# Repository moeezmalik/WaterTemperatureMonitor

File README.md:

# WaterTemperatureMonitor
 Simple system that monitors the temperature of bath water and displays it on a pair of 7 segment display.

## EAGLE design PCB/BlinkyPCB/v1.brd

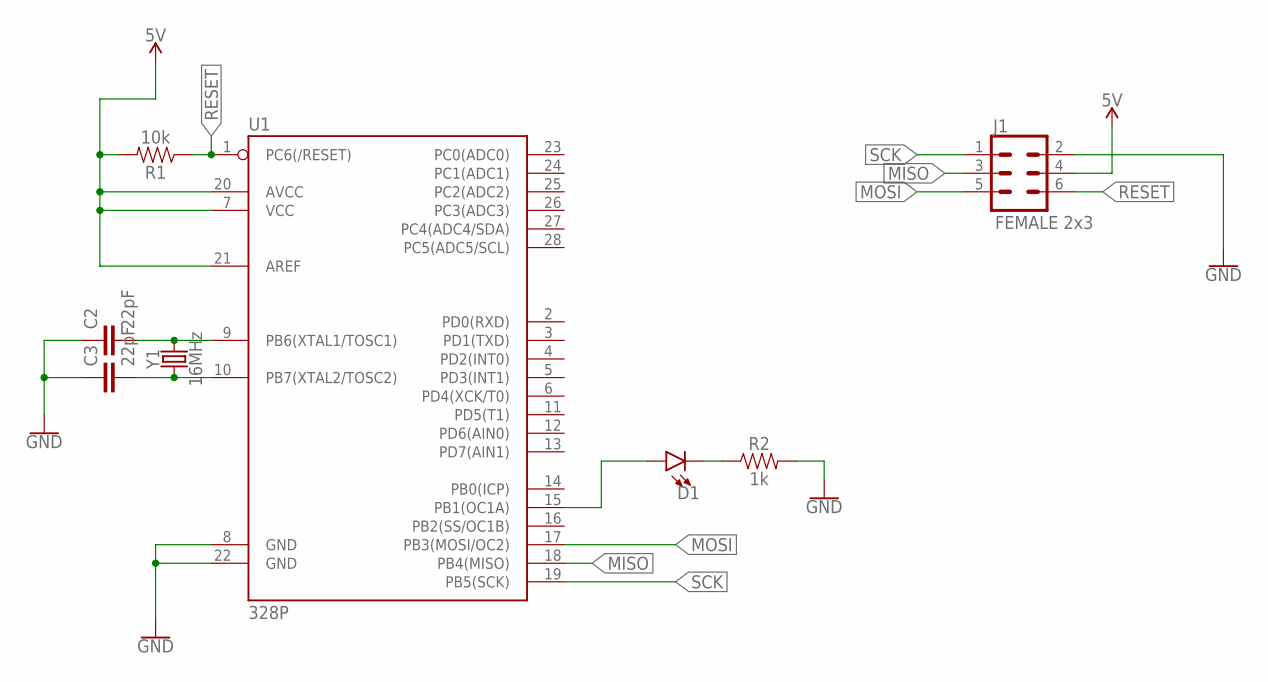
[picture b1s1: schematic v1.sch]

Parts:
C2, C3: 22pF; CAP-PTH-2.54
D1: LED3MM; LED_3MM
J1: FEMALE 2x3; 2X3
R1: 10k; AXIAL-0.3
R2: 1k; AXIAL-0.3
U1: 328P; DIP28
Y1: 16MHz; HC49US

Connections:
5V: J1.4, R1.P$2 (2), U1.7 (VCC), U1.20 (AVCC), U1.21 (AREF)
GND: C2.1, C3.1, J1.2, R2.P$2 (2), U1.8 (GND), U1.22 (GND)
MISO: J1.3, U1.18 (PB4(MISO))
MOSI: J1.5, U1.17 (PB3(MOSI/OC2))
unnamed: D1.A, U1.15 (PB1(OC1A))
unnamed: D1.K (C), R2.P$1 (1)
unnamed: C2.2, U1.9 (PB6(XTAL1/TOSC1)), Y1.2
unnamed: C3.2, U1.10 (PB7(XTAL2/TOSC2)), Y1.1
RESET: J1.6, R1.P$1 (1), U1.1 (PC6(/RESET))
SCK: J1.1, U1.19 (PB5(SCK))

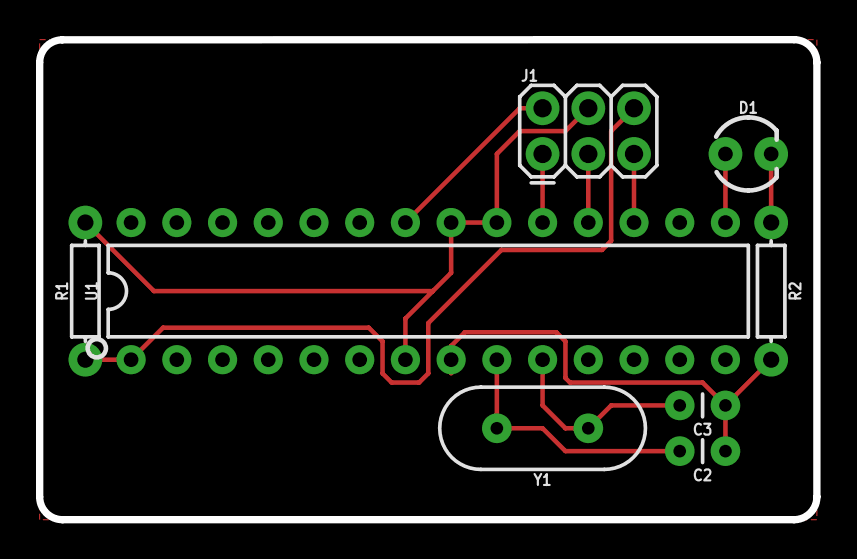
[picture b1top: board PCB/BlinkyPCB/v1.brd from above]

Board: 2 copper layers, 43.2 x 26.7 mm, 8 parts (0 on the bottom side), 10 nets.

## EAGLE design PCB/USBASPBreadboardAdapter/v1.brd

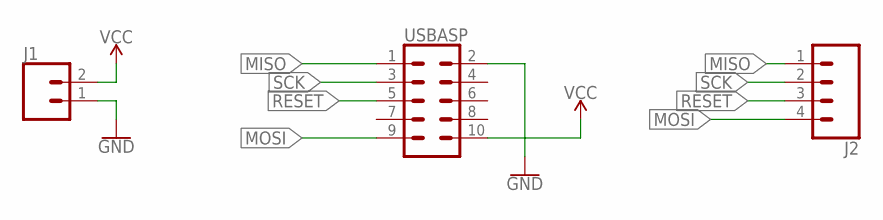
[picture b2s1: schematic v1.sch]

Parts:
J1: CONN_02; 1X02
J2: CONN_04; 1X04
USBASP: CONN_05X2PTH; 2X5

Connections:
GND: J1.1, USBASP.2
MISO: J2.1, USBASP.1
MOSI: J2.4, USBASP.9
RESET: J2.3, USBASP.5
SCK: J2.2, USBASP.3
VCC: J1.2, USBASP.10

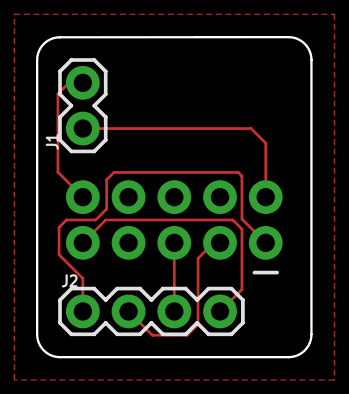
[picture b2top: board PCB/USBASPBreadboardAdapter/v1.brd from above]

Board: 2 copper layers, 15.2 x 17.8 mm, 3 parts (1 on the bottom side), 6 nets.

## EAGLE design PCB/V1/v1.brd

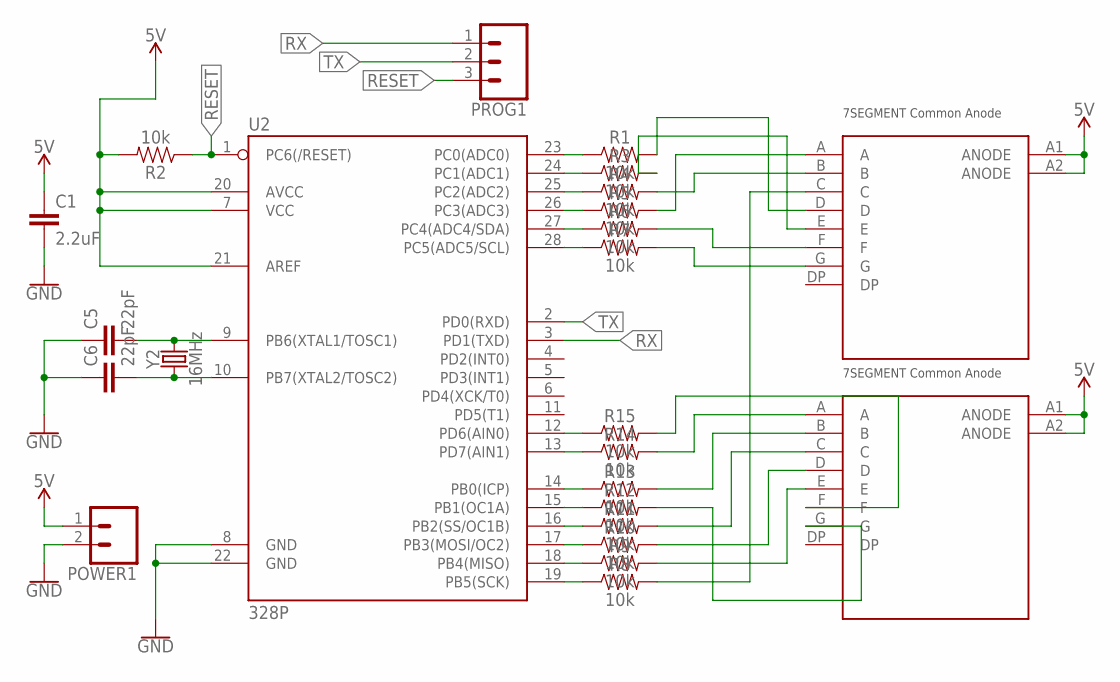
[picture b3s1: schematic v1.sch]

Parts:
C1: 2.2uF; 1206
C5, C6: 22pF; CAP-PTH-2.54
POWER1: CONN_02; 1X02
PROG1: CONN_03; 1X03
R1, R3, R4, R5, R6, R7, R8, R9, R10, R11, R12, R13, R14, R15: 10k; 0805
R2: 10k; AXIAL-0.3
U2: 328P; DIP28
U$1, U$2: 7SEGMENTCA
Y2: 16MHz; HC49US

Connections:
5V: C1.1, POWER1.1, R2.P$2 (2), U2.7 (VCC), U2.20 (AVCC), U2.21 (AREF), U$1.A1 (ANODE), U$1.A2 (ANODE), U$2.A1 (ANODE), U$2.A2 (ANODE)
GND: C1.2, C5.1, C6.1, POWER1.2, U2.8 (GND), U2.22 (GND)
unnamed: C5.2, U2.9 (PB6(XTAL1/TOSC1)), Y2.2
unnamed: C6.2, U2.10 (PB7(XTAL2/TOSC2)), Y2.1
unnamed: R1.1, U2.23 (PC0(ADC0))
unnamed: R3.1, U2.24 (PC1(ADC1))
unnamed: R4.1, U2.25 (PC2(ADC2))
unnamed: R5.1, U2.26 (PC3(ADC3))
unnamed: R6.1, U2.27 (PC4(ADC4/SDA))
unnamed: R7.1, U2.28 (PC5(ADC5/SCL))
unnamed: R7.2, U$1.G
unnamed: R6.2, U$1.F
unnamed: R5.2, U$1.A
unnamed: R4.2, U$1.B
unnamed: R3.2, U$1.E
unnamed: R1.2, U$1.D
unnamed: R8.1, U2.19 (PB5(SCK))
unnamed: R8.2, U$1.C
unnamed: R12.1, U2.15 (PB1(OC1A))
unnamed: R11.1, U2.16 (PB2(SS/OC1B))
unnamed: R10.1, U2.17 (PB3(MOSI/OC2))
unnamed: R9.1, U2.18 (PB4(MISO))
unnamed: R9.2, U$2.E
unnamed: R10.2, U$2.D
unnamed: R11.2, U$2.C
unnamed: R12.2, U$2.G
unnamed: R15.1, U2.12 (PD6(AIN0))
unnamed: R14.1, U2.13 (PD7(AIN1))
unnamed: R13.1, U2.14 (PB0(ICP))
unnamed: R15.2, U$2.F
unnamed: R14.2, U$2.A
unnamed: R13.2, U$2.B
RESET: PROG1.3, R2.P$1 (1), U2.1 (PC6(/RESET))
RX: PROG1.1, U2.3 (PD1(TXD))
TX: PROG1.2, U2.2 (PD0(RXD))

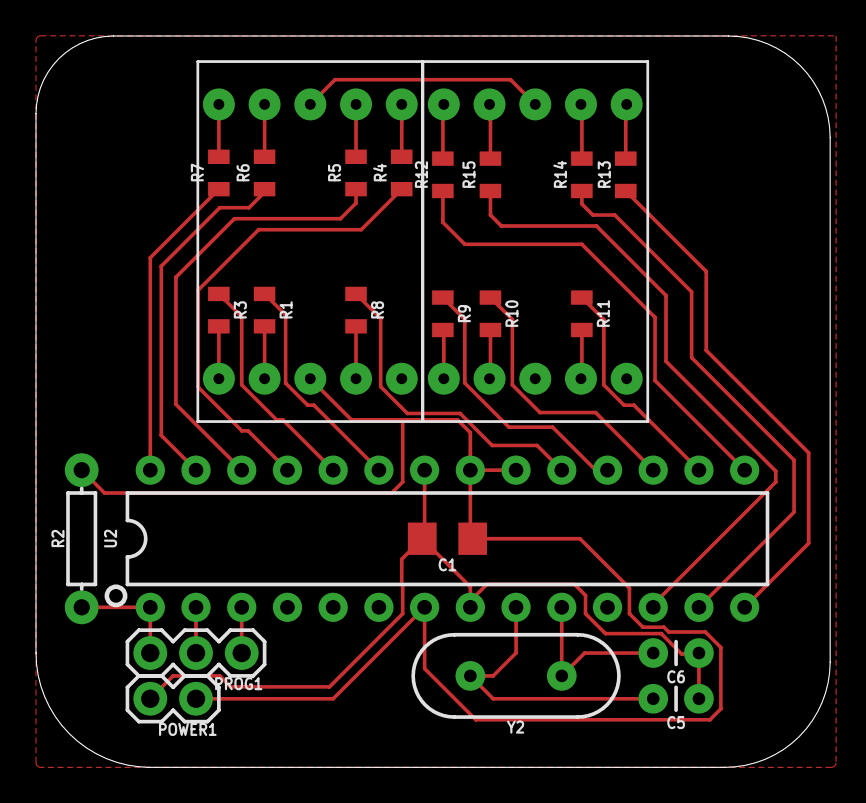
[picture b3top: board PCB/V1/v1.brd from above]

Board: 2 copper layers, 44.1 x 40.6 mm, 24 parts (0 on the bottom side), 35 nets.

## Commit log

2019-12-13 Checking 7 segment display footprint
2019-12-13 first pcb to test 7 segment, temperature sensor not added yet.
2019-12-26 Breadboard Programmer Adapter PCB

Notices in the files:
parts and their libraries:
SparkFun-Capacitors: Licensing: Creative Commons ShareAlike 4.0 International - https://creativecommons.org/licenses/by-sa/4.0
